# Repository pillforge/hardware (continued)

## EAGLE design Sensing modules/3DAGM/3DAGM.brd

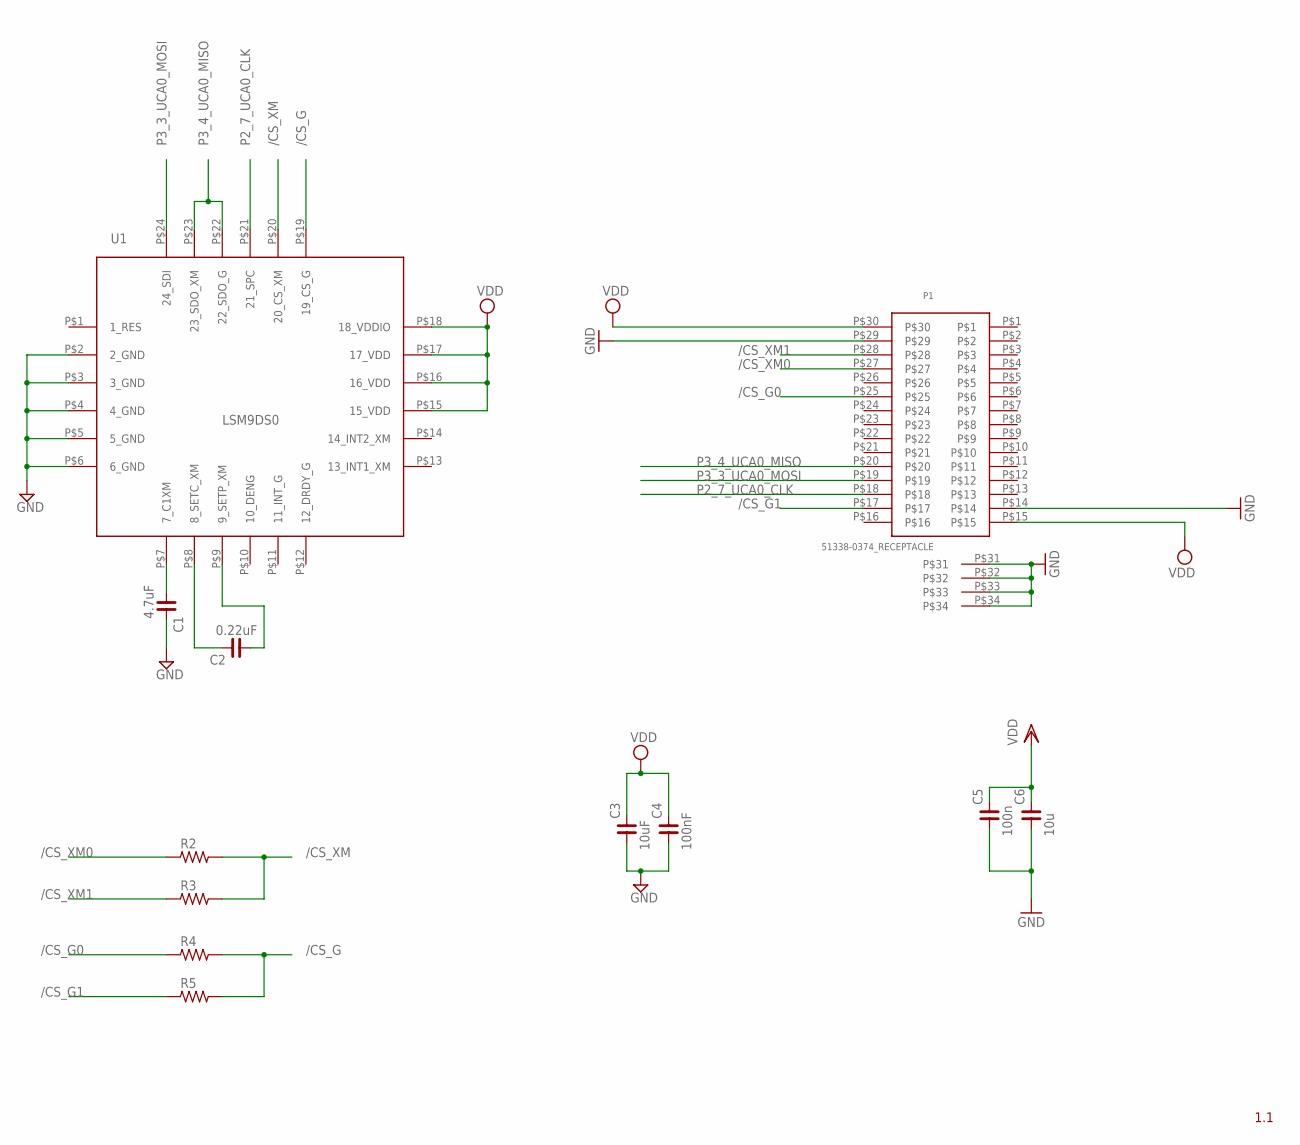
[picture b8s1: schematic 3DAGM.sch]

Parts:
C1: 4.7uF; C0402
C2: 0.22uF; C0402
C3: 10uF; C0402
C4: 100nF; C0402
C5: 100n; C0402
C6: 10u; C0402
P1: 51338-0374_RECEPTACLE
R2, R3, R4, R5: R_0402; R0402
U$1: LSM9DS09DOFS0; LGA24(4X4X1)

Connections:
/CS_G: R4.2, R5.2, U$1.P$19 (19_CS_G)
/CS_G0: P1.P$25, R4.1
/CS_G1: P1.P$17, R5.1
/CS_XM: R2.2, R3.2, U$1.P$20 (20_CS_XM)
/CS_XM0: P1.P$27, R2.1
/CS_XM1: P1.P$28, R3.1
GND: C1.2, C3.1, C4.1, C5.1, C6.1, P1.P$14, P1.P$29, P1.P$31, P1.P$32, P1.P$33, P1.P$34, U$1.P$2 (2_GND), U$1.P$3 (3_GND), U$1.P$4 (4_GND), U$1.P$5 (5_GND), U$1.P$6 (6_GND)
unnamed: C1.1, U$1.P$7 (7_C1XM)
unnamed: C2.2, U$1.P$8 (8_SETC_XM)
unnamed: C2.1, U$1.P$9 (9_SETP_XM)
P2_7_UCA0_CLK: P1.P$18, U$1.P$21 (21_SPC)
P3_3_UCA0_MOSI: P1.P$19, U$1.P$24 (24_SDI)
P3_4_UCA0_MISO: P1.P$20, U$1.P$22 (22_SDO_G), U$1.P$23 (23_SDO_XM)
VDD: C3.2, C4.2, C5.2, C6.2, P1.P$15, P1.P$30, U$1.P$15 (15_VDD), U$1.P$16 (16_VDD), U$1.P$17 (17_VDD), U$1.P$18 (18_VDDIO)

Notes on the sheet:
1.1

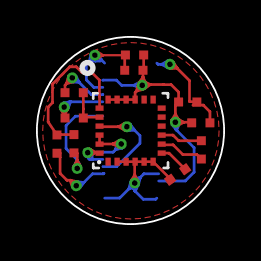
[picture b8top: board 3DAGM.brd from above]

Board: 2 copper layers, 10.4 x 10.4 mm, 12 parts (1 on the bottom side), 14 nets.

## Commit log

2013-07-29 Initial import
2015-05-01 Add updated modules with more documentation
2016-08-18 Updated Sensing Modules
    Edited soldering pads, labeled each module
